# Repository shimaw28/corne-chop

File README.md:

# corne-chop
blueprints of hand-made keyboard "corne-chop" inspired from "crkbd" by foostan.

please see https://github.com/foostan/crkbd for buildguides

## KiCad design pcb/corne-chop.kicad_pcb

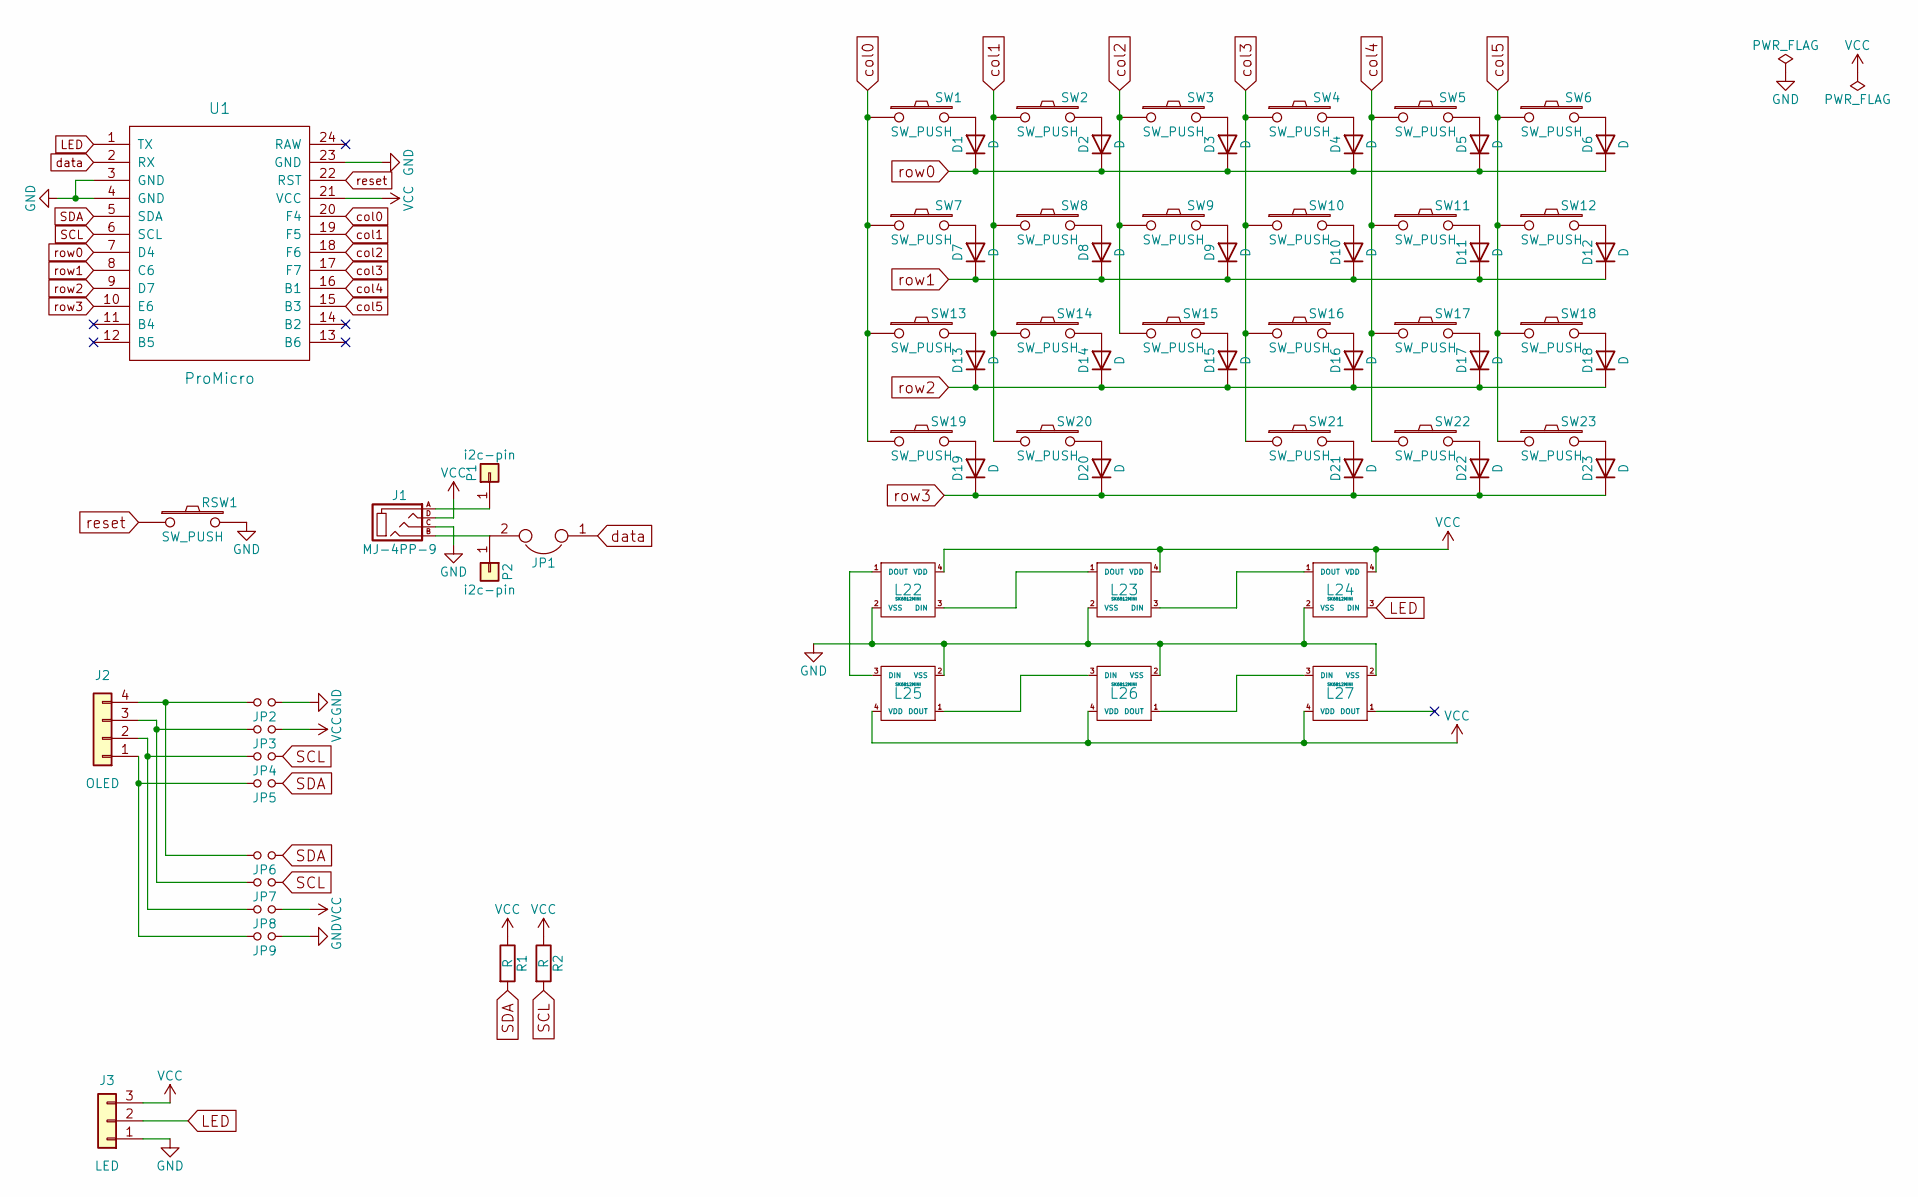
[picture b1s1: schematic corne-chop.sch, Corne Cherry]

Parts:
D1, D2, D3, D4, D5, D6, D7, D8, D9, D10, D11, D12, D13, D14, D15, D16, D17, D18, D19, D20, D21, D22, D23: D; D3_SMD
J1: MJ-4PP-9
J2: OLED
J3: LED; StripLED_rev
JP1: JPC2
JP2, JP3, JP4, JP5, JP6, JP7, JP8, JP9: Jumper
L22, L23, L24, L25, L26, L27: SK6812MINI; SK6812MINI_underglow_rev
P1, P2: i2c-pin; 1pin_conn
R1, R2: R
RSW1: SW_PUSH; ResetSW
SW1, SW2, SW3, SW4, SW5, SW6, SW7, SW8, SW9, SW10, SW11, SW12, SW13, SW14, SW15, SW16, SW17, SW18, SW19, SW20, SW21, SW22: SW_PUSH; CherryMX_Choc_Hotswap
SW23: SW_PUSH; CherryMX_Choc_Hotswap_1.5u
U1: ProMicro; ProMicro_v2

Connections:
GND: J1.C, J3.1, JP2.1, JP9.1, L22.2 (VSS), L23.2 (VSS), L24.2 (VSS), L25.2 (VSS), L26.2 (VSS), L27.2 (VSS), RSW1.2, U1.3 (GND), U1.4 (GND), U1.23 (GND)
LED: J3.2, L24.3 (DIN), U1.1 (TX)
unnamed: D1.2 (A), SW1.2
unnamed: D2.2 (A), SW2.2
unnamed: D3.2 (A), SW3.2
unnamed: D4.2 (A), SW4.2
unnamed: D5.2 (A), SW5.2
unnamed: D6.2 (A), SW6.2
unnamed: D7.2 (A), SW7.2
unnamed: D8.2 (A), SW8.2
unnamed: D9.2 (A), SW9.2
unnamed: D10.2 (A), SW10.2
unnamed: D11.2 (A), SW11.2
unnamed: D12.2 (A), SW12.2
unnamed: D13.2 (A), SW13.2
unnamed: D14.2 (A), SW14.2
unnamed: D15.2 (A), SW15.2
unnamed: D16.2 (A), SW16.2
unnamed: D17.2 (A), SW17.2
unnamed: D18.2 (A), SW18.2
unnamed: D19.2 (A), SW19.2
unnamed: D20.2 (A), SW20.2
unnamed: D21.2 (A), SW21.2
unnamed: D22.2 (A), SW22.2
unnamed: D23.2 (A), SW23.2
unnamed: J1.A, P1.1
unnamed: J1.B, JP1.2, P2.1
unnamed: J2.1, JP5.2, JP9.2
unnamed: J2.2, JP4.2, JP8.2
unnamed: J2.3, JP3.2, JP7.2
unnamed: J2.4, JP2.2, JP6.2
unnamed: L22.1 (DOUT), L25.3 (DIN)
unnamed: L22.3 (DIN), L23.1 (DOUT)
unnamed: L23.3 (DIN), L24.1 (DOUT)
unnamed: L25.1 (DOUT), L26.3 (DIN)
unnamed: L26.1 (DOUT), L27.3 (DIN)
SCL: JP4.1, JP7.1, R2.2, U1.6 (SCL)
SDA: JP5.1, JP6.1, R1.2, U1.5 (SDA)
VCC: J1.D, J3.3, JP3.1, JP8.1, L22.4 (VDD), L23.4 (VDD), L24.4 (VDD), L25.4 (VDD), L26.4 (VDD), L27.4 (VDD), R1.1, R2.1, U1.21 (VCC)
col0: SW1.1, SW7.1, SW13.1, SW19.1, U1.20 (F4)
col1: SW2.1, SW8.1, SW14.1, SW20.1, U1.19 (F5)
col2: SW3.1, SW9.1, SW15.1, U1.18 (F6)
col3: SW4.1, SW10.1, SW16.1, SW21.1, U1.17 (F7)
col4: SW5.1, SW11.1, SW17.1, SW22.1, U1.16 (B1)
col5: SW6.1, SW12.1, SW18.1, SW23.1, U1.15 (B3)
data: JP1.1, U1.2 (RX)
reset: RSW1.1, U1.22 (RST)
row0: D1.1 (K), D2.1 (K), D3.1 (K), D4.1 (K), D5.1 (K), D6.1 (K), U1.7 (D4)
row1: D7.1 (K), D8.1 (K), D9.1 (K), D10.1 (K), D11.1 (K), D12.1 (K), U1.8 (C6)
row2: D13.1 (K), D14.1 (K), D15.1 (K), D16.1 (K), D17.1 (K), D18.1 (K), U1.9 (D7)
row3: D19.1 (K), D20.1 (K), D21.1 (K), D22.1 (K), D23.1 (K), U1.10 (E6)

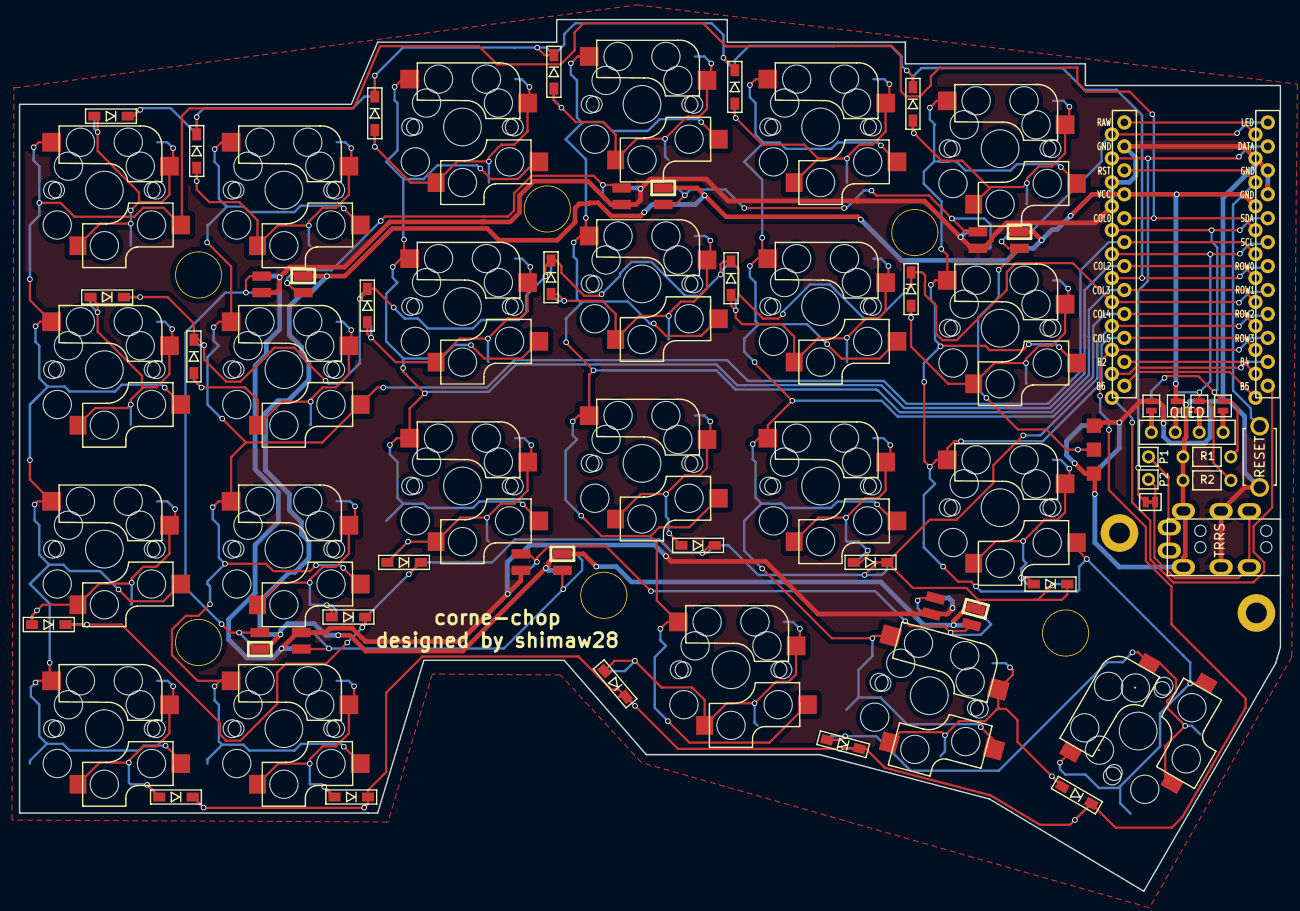
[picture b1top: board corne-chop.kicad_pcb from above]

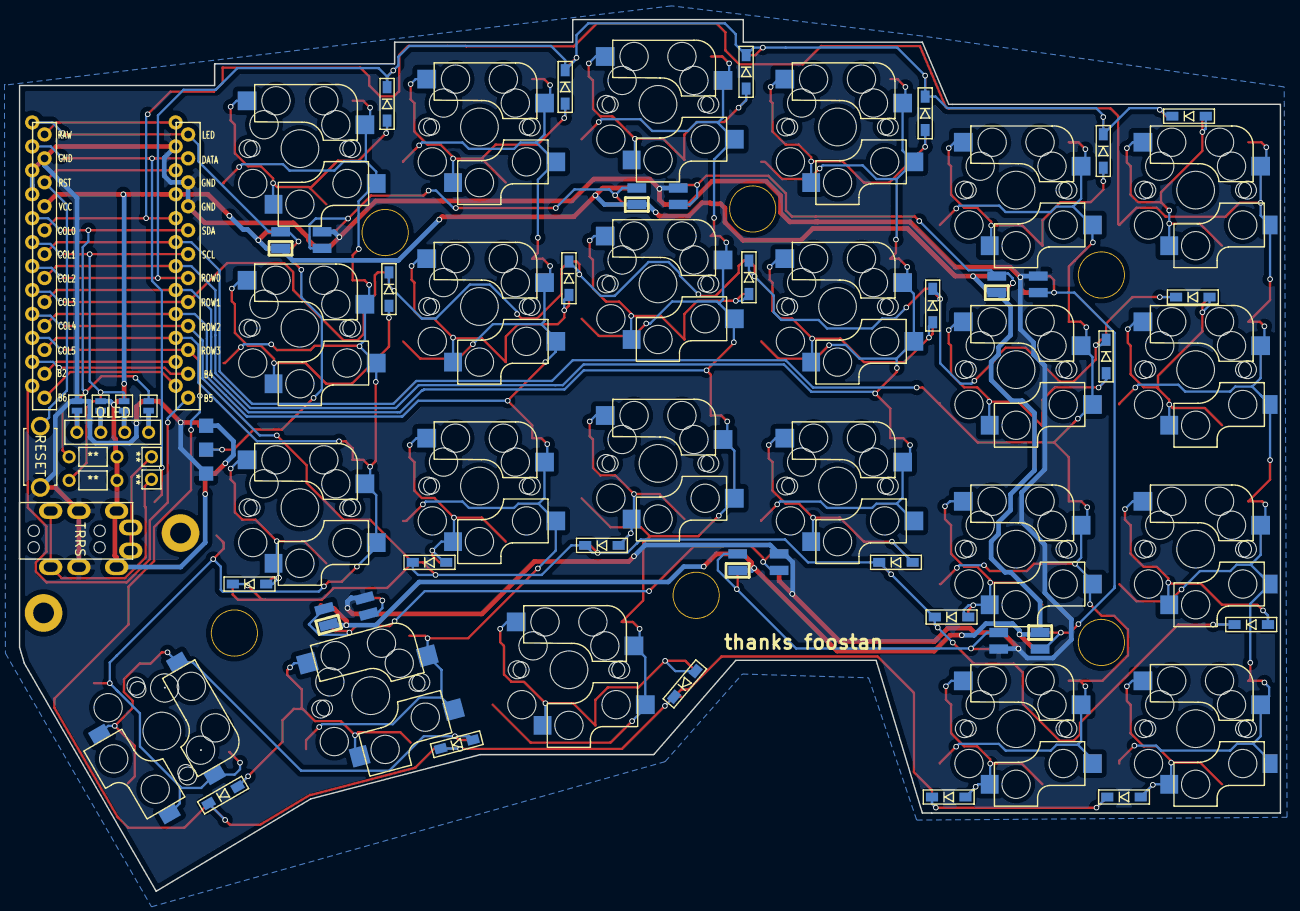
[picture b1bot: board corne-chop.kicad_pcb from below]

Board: 2 copper layers, 133.8 x 92.5 mm, 76 parts (4 on the bottom side), 51 nets.

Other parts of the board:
Ref**: Val**; HOLE
Ref**#2, Ref**#3, Ref**#4, Ref**#5, Ref**#6: Val**; HOLE
